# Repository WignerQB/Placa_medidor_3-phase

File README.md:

# Placa_medidor_3-phase
Projeto da placa PCB do medidor inteligente da fase 2

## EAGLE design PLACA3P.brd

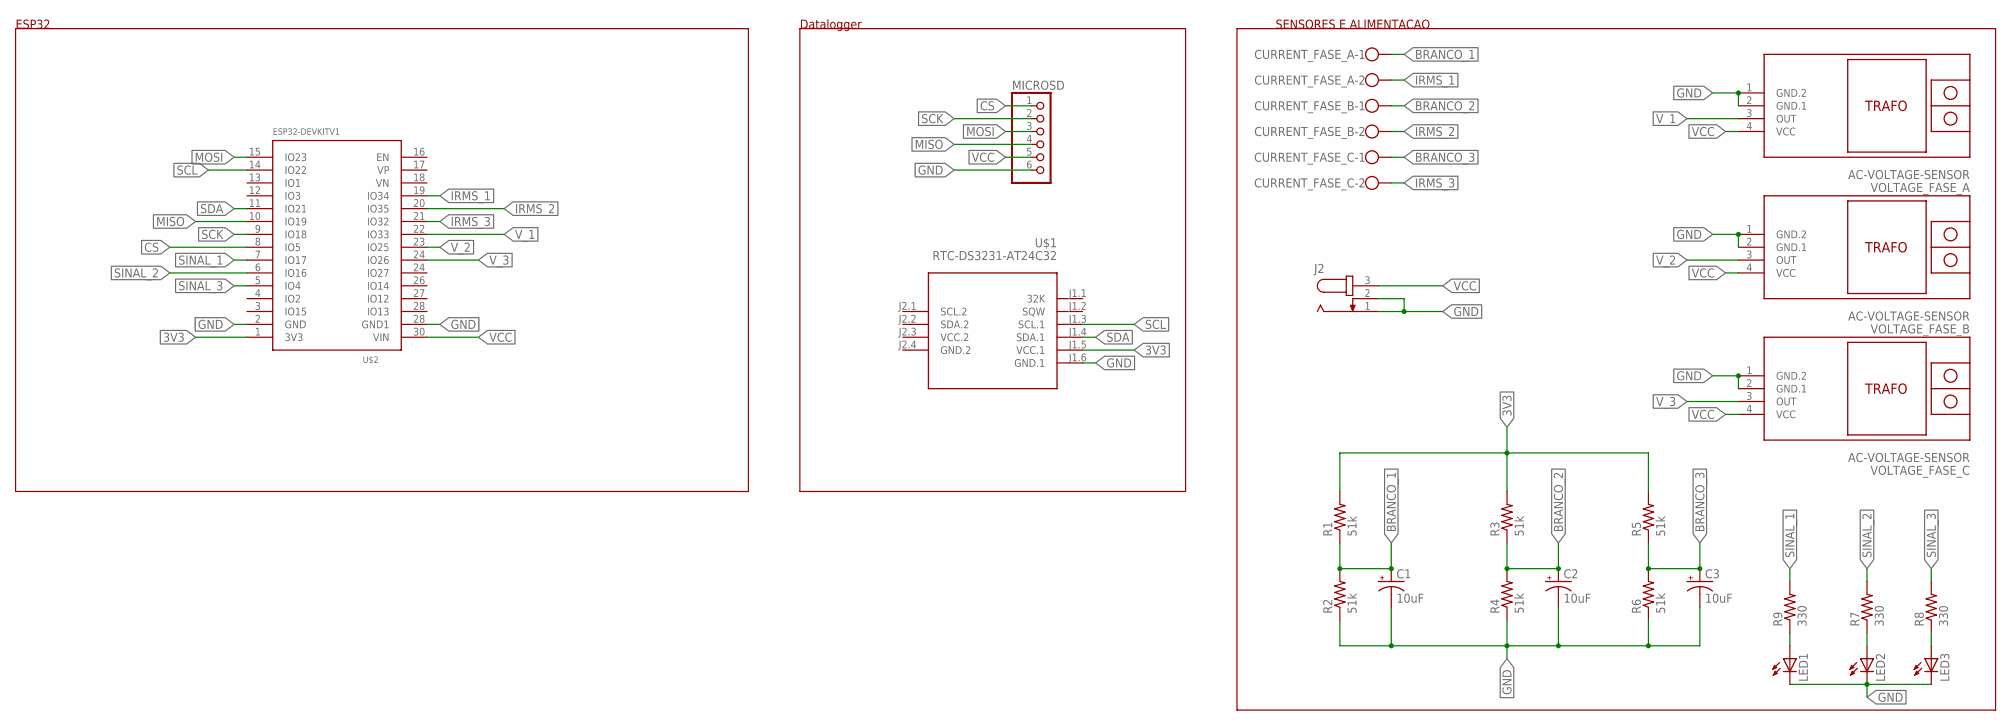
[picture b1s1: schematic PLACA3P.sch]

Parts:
C1, C2, C3: 10uF; E2-4
CURRENT_FASE_A: W237-102
CURRENT_FASE_B: W237-102
CURRENT_FASE_C: W237-102
J2: JACK-PLUG1; SPC4078
LED1, LED2, LED3: LED5MM
MICROSD: PINHD-1X6B; 1X06-BIG
R1, R2, R3, R4, R5, R6: 51k; 0207/12
R7, R8, R9: 330; 0207/12
U$1: RTC-DS3231-AT24C32
U$2: ESP32DEVKITV1; ESP32-DEVKITV1
VOLTAGE_FASE_A: AC-VOLTAGE-SENSOR
VOLTAGE_FASE_B: AC-VOLTAGE-SENSOR
VOLTAGE_FASE_C: AC-VOLTAGE-SENSOR

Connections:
3V3: R1.2, R3.2, R5.2, U$1.J1.5 (VCC.1), U$2.1 (3V3)
BRANCO_1: C1.+, CURRENT_FASE_A.1, R1.1, R2.2
BRANCO_2: C2.+, CURRENT_FASE_B.1, R3.1, R4.2
BRANCO_3: C3.+, CURRENT_FASE_C.1, R5.1, R6.2
CS: MICROSD.1, U$2.8 (IO5)
GND: C1.-, C2.-, C3.-, J2.1, J2.2, LED1.K (C), LED2.K (C), LED3.K (C), MICROSD.6, R2.1, R4.1, R6.1, U$1.J1.6 (GND.1), U$2.2 (GND), U$2.28 (IO13), VOLTAGE_FASE_A.1 (GND.2), VOLTAGE_FASE_A.2 (GND.1), VOLTAGE_FASE_B.1 (GND.2), VOLTAGE_FASE_B.2 (GND.1), VOLTAGE_FASE_C.1 (GND.2), VOLTAGE_FASE_C.2 (GND.1)
GND.2: U$1.J2.4 (GND.2)
IRMS_1: CURRENT_FASE_A.2, U$2.19 (IO34)
IRMS_2: CURRENT_FASE_B.2, U$2.20 (IO35)
IRMS_3: CURRENT_FASE_C.2, U$2.21 (IO32)
MISO: MICROSD.4, U$2.10 (IO19)
MOSI: MICROSD.3, U$2.15 (IO23)
unnamed: LED1.A, R9.1
unnamed: LED2.A, R7.1
unnamed: LED3.A, R8.1
SCK: MICROSD.2, U$2.9 (IO18)
SCL: U$1.J1.3 (SCL.1), U$2.14 (IO22)
SDA: U$1.J1.4 (SDA.1), U$2.11 (IO21)
SINAL_1: R9.2, U$2.7 (IO17)
SINAL_2: R7.2, U$2.6 (IO16)
SINAL_3: R8.2, U$2.5 (IO4)
VCC: J2.3, MICROSD.5, U$2.30 (VIN), VOLTAGE_FASE_A.4 (VCC), VOLTAGE_FASE_B.4 (VCC), VOLTAGE_FASE_C.4 (VCC)
VCC.2: U$1.J2.3 (VCC.2)
V_1: U$2.22 (IO33), VOLTAGE_FASE_A.3 (OUT)
V_2: U$2.23 (IO25), VOLTAGE_FASE_B.3 (OUT)
V_3: U$2.24 (IO27), VOLTAGE_FASE_C.3 (OUT)

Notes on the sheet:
ESP32
Datalogger
SENSORES E ALIMENTACAO

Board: 2 copper layers, 25 parts (0 on the bottom side), 24 nets, no tracks yet.

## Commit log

2021-03-23 Versao1

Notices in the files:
parts and their libraries:
diy-modules: Released under the Creative Commons Attribution 4.0 International License: http://creativecommons.org/licenses/by/4.0
